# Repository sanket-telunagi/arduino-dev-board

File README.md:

# Atmega Development Board

A development board created specifically for the Atmega8A microcontroller, designed and implemented using KiCAD. This board encompasses all necessary SMD components along with a USB to TTL converter, facilitating code dumping. 

## Key Features

- **Comprehensive Design:** All SMD components integrated for the Atmega8A microcontroller.
- **USB to TTL Converter:** Facilitates easy code dumping and debugging.
- **Exposed Pinouts:** All required pinouts are exposed, allowing easy external connections.
- **Hand-Soldered Components:** Carefully hand-soldered components ensuring reliability.
  
## Uses

This development board is particularly useful for:

- **Sensor Interfacing:** Ideal for interfacing various sensors for data acquisition.
- **Servo Control:** Capable of controlling servos for various mechanical applications.
- **General Controller:** Can function as a versatile controller for multiple projects.

## Tools Used

- **KiCAD:** The entire board design and layout were developed using KiCAD, ensuring an open-source and accessible approach to hardware design.

## Getting Started

These are KiCAD designs one can use these designs with the latest version of KiCAD

## Credits

- **[Sanket Telunagi]:** Project creator/designer.

## License

Atmega8A-Dev-Board © 2023 by Sanket Telunagi is licensed under CC BY 4.0 

## Output

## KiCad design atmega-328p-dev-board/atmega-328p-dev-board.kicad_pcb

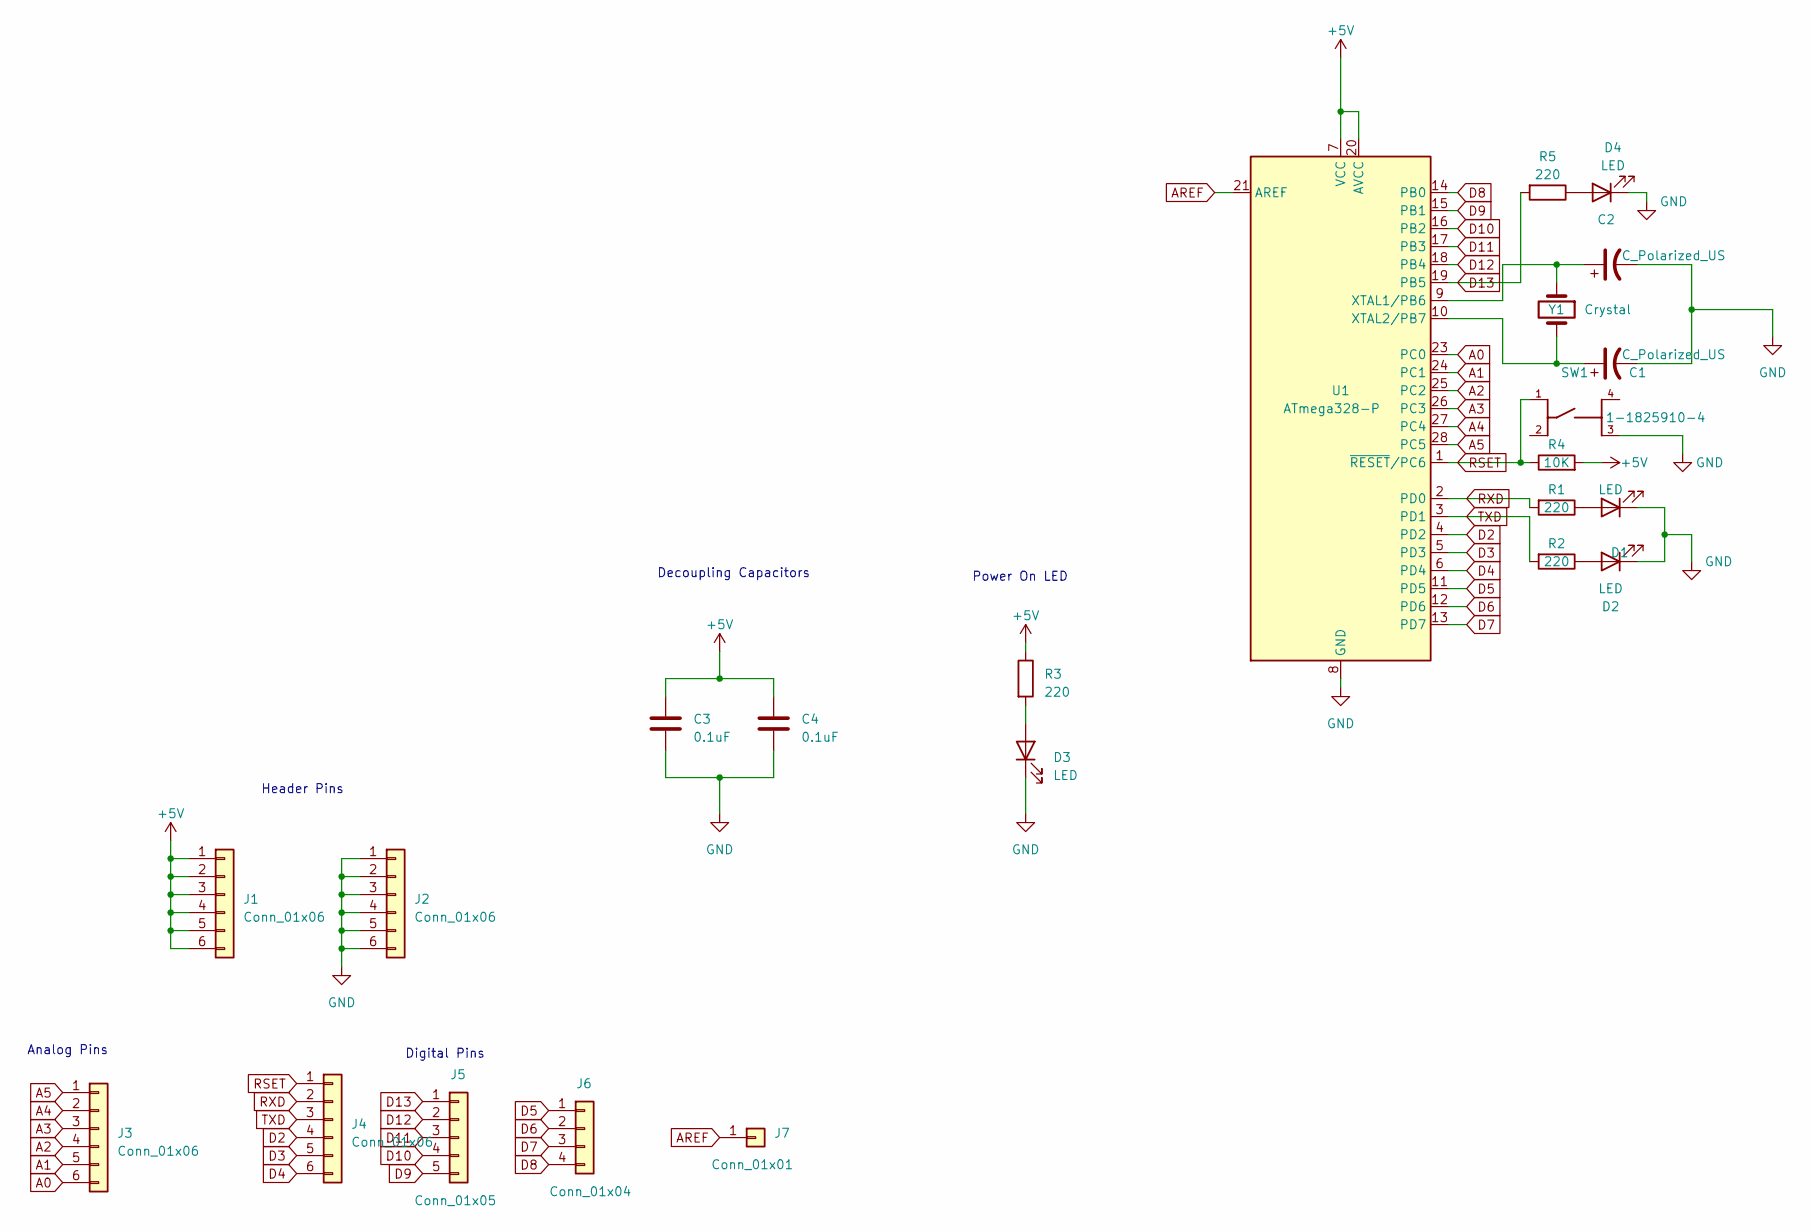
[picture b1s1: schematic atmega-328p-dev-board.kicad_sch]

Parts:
C1, C2: C_Polarized_US; CP_Radial_Tantal_D4.5mm_P5.00mm
C3, C4: 0.1uF; C_Radial_D10.0mm_H12.5mm_P5.00mm
D1, D2, D3, D4: LED; LED_D5.0mm
J1, J2, J3, J4: Conn_01x06; PinHeader_1x06_P2.54mm_Vertical
J5: Conn_01x05; PinHeader_1x05_P2.54mm_Vertical
J6: Conn_01x04; R_Axial_DIN0614_L14.3mm_D5.7mm_P15.24mm_Horizontal
J7: Conn_01x01; PinSocket_1x01_P2.54mm_Vertical
R1, R2, R3, R5: 220; R_Axial_DIN0207_L6.3mm_D2.5mm_P7.62mm_Horizontal
R4: 10K; R_Axial_DIN0207_L6.3mm_D2.5mm_P7.62mm_Horizontal
SW1: 1-1825910-4; TE_1-1825910-4; PARTREV C10
U1: ATmega328-P; DIP-28_W7.62mm
Y1: Crystal; Crystal_HC49-U_Vertical

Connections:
+5V: C3.1, C4.1, J1.1, J1.2, J1.3, J1.4, J1.5, J1.6, R3.1, R4.2, U1.7 (VCC), U1.20 (AVCC)
A0: J3.6, U1.23 (PC0)
A1: J3.5, U1.24 (PC1)
A2: J3.4, U1.25 (PC2)
A3: J3.3, U1.26 (PC3)
A4: J3.2, U1.27 (PC4)
A5: J3.1, U1.28 (PC5)
AREF: J7.1, U1.21 (AREF)
D2: J4.4, U1.4 (PD2)
D3: J4.5, U1.5 (PD3)
D4: J4.6, U1.6 (PD4)
D5: J6.1, U1.11 (PD5)
D6: J6.2, U1.12 (PD6)
D7: J6.3, U1.13 (PD7)
D8: J6.4, U1.14 (PB0)
D9: J5.5, U1.15 (PB1)
D10: J5.4, U1.16 (PB2)
D11: J5.3, U1.17 (PB3)
D12: J5.2, U1.18 (PB4)
D13: J5.1, R5.2, U1.19 (PB5)
GND: C1.2, C2.2, C3.2, C4.2, D1.1 (K), D2.1 (K), D3.1 (K), D4.1 (K), J2.1, J2.2, J2.3, J2.4, J2.5, J2.6, SW1.3, U1.8 (GND), U1.22 (GND)
unnamed: D1.2 (A), R1.1
unnamed: D2.2 (A), R2.1
unnamed: D3.2 (A), R3.2
unnamed: D4.2 (A), R5.1
unnamed: C2.1, U1.9 (XTAL1/PB6), Y1.1
unnamed: C1.1, U1.10 (XTAL2/PB7), Y1.2
RSET: J4.1, R4.1, SW1.1, U1.1 (~RESET/PC6)
RXD: J4.2, R1.2, U1.2 (PD0)
TXD: J4.3, R2.2, U1.3 (PD1)

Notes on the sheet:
Analog Pins
Decoupling Capacitors
Power On LED
Header Pins
Digital Pins

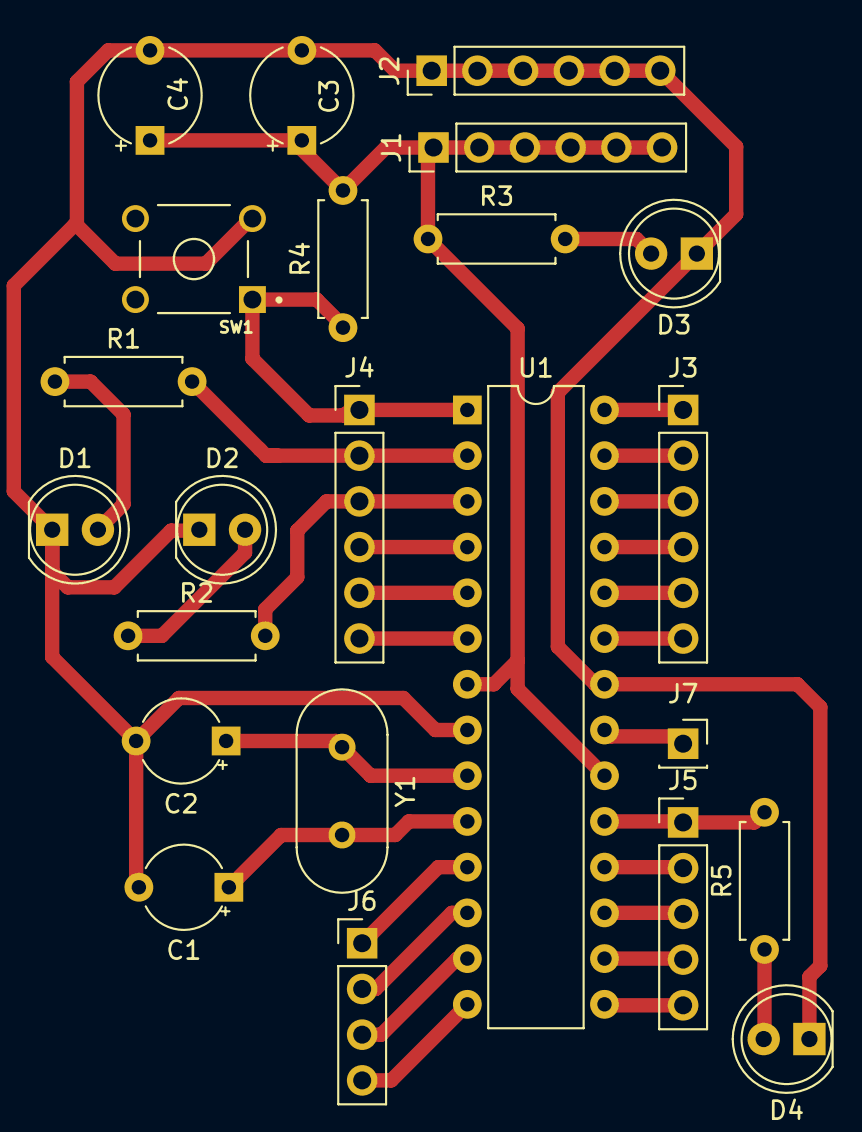
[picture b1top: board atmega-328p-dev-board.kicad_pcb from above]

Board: 2 copper layers, 23 parts (0 on the bottom side), 30 nets.

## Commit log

2023-11-17 Dev board Complete
2023-11-17 atmega 8A dev board layout
